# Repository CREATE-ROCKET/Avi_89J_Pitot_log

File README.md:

# 89Jのピトー管基板用です

## 現在の予定
基本的にFree RTOSでのタスク機能を利用して
 - ピトー管からデーターを得るタスク
 - それを他に送るタスク(CAN、 SPIFlash、 パリティ)
 - CANを送信するタスク
 - SPIFlashに書き込むタスク
 - MicroSDに書き込むタスク

の4つをタスクとして動作させたい。
MicroSDにログを書き込むようのタスクも作るか考え中

```mermaid
flowchart TB
  node_1("getPitotData")
  node_2("sendDataToEveryIC")
  node_3("writeDataToFlash")
  node_4("sendDataByCan")
  node_6("writeDataToSD")
  node_2 --> node_4
  node_2 --> node_3
  node_1 --> node_2
  node_2 --> node_6
```

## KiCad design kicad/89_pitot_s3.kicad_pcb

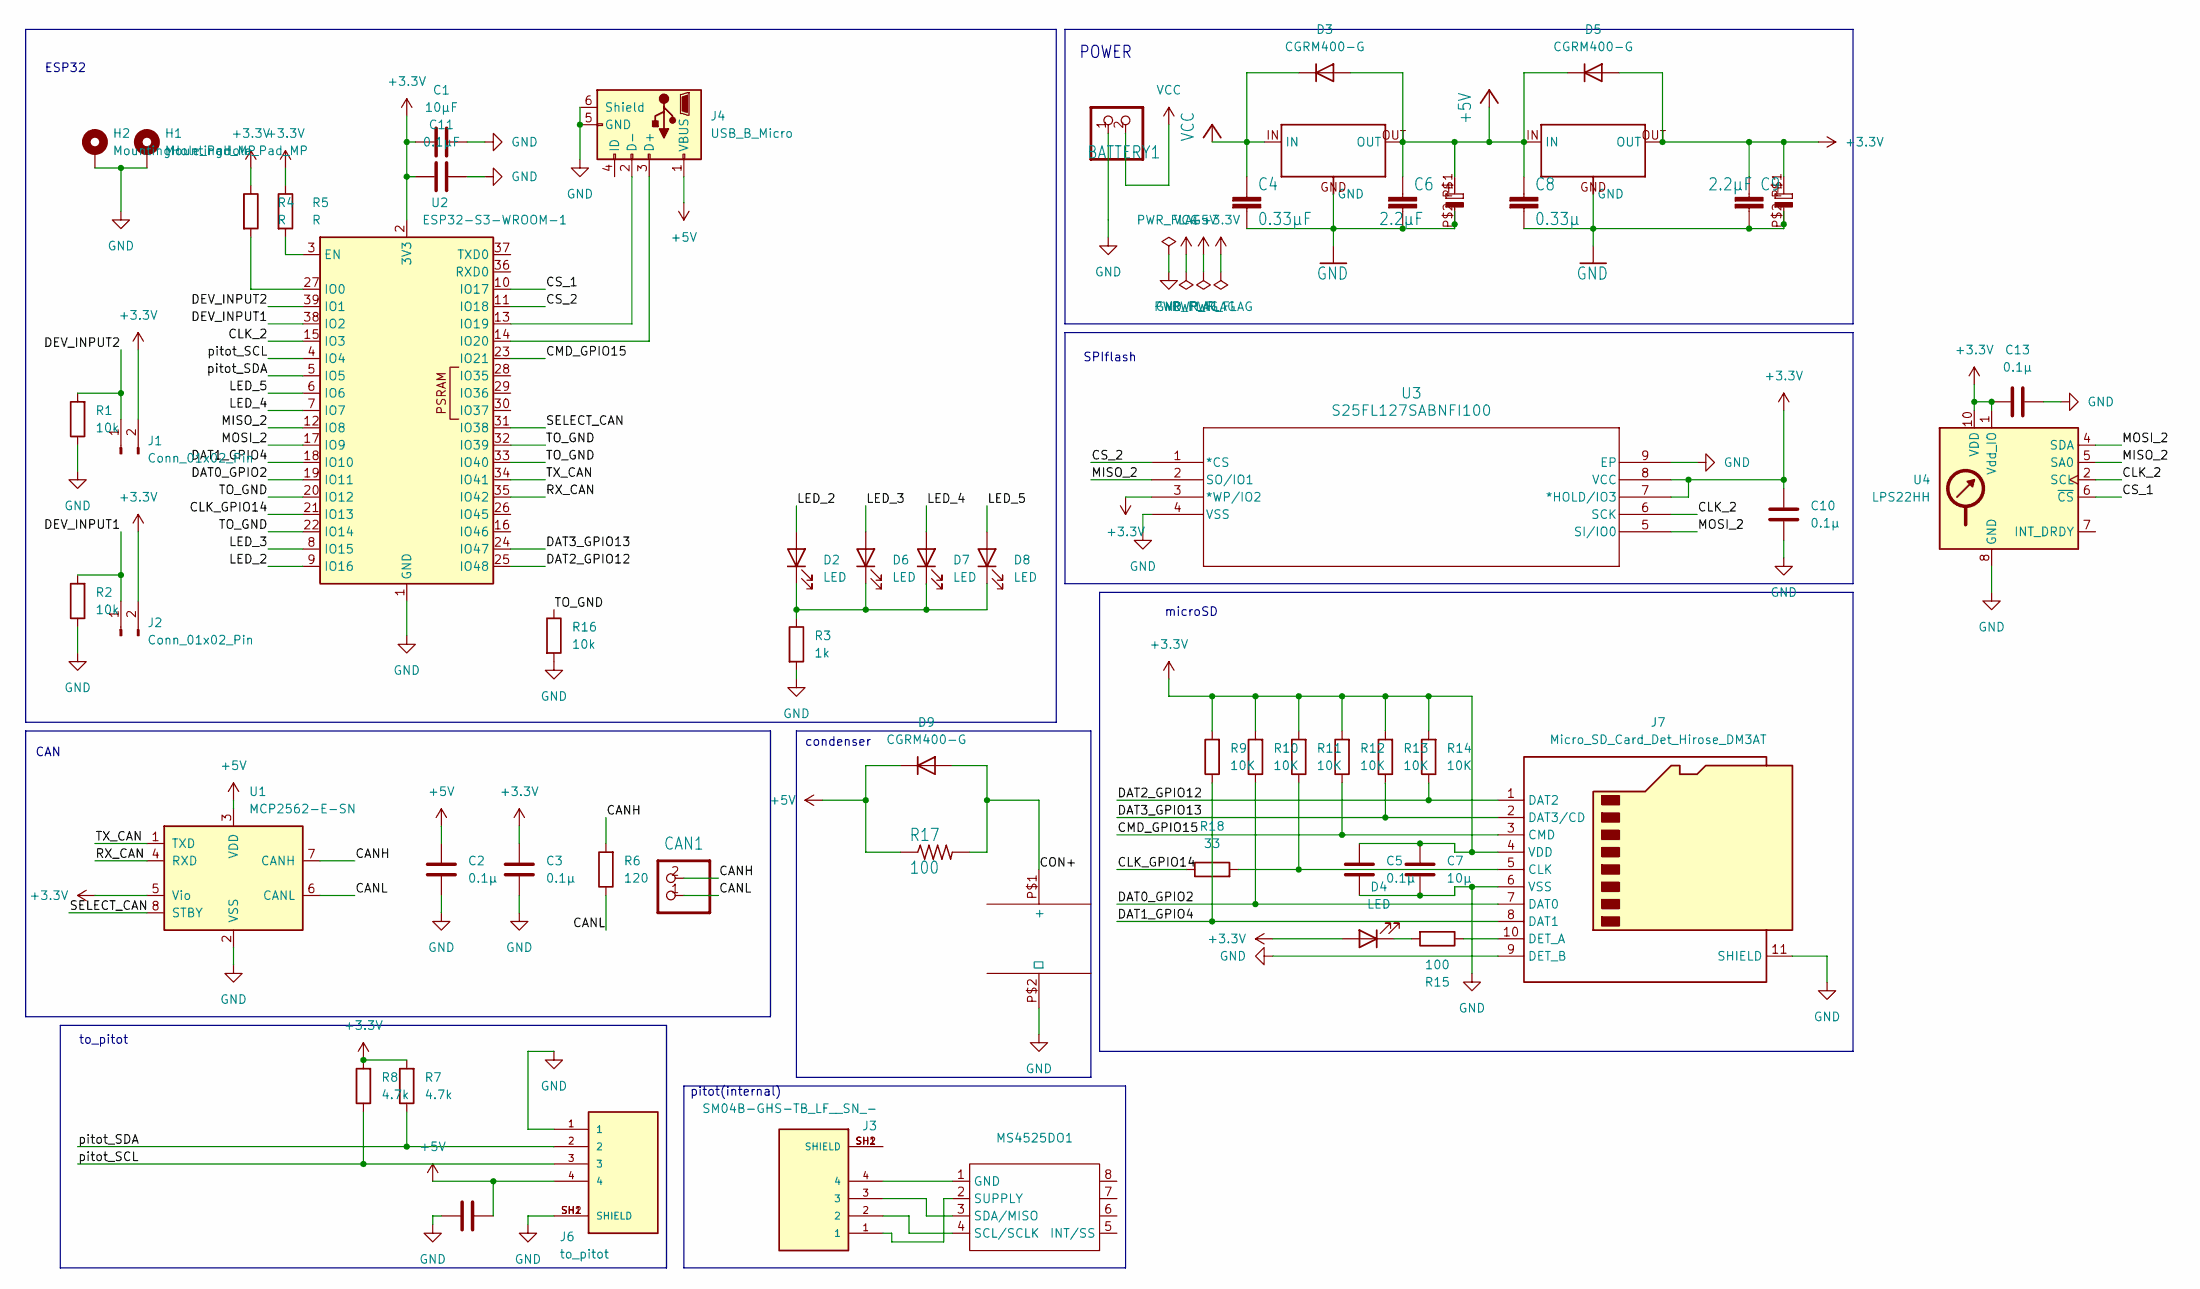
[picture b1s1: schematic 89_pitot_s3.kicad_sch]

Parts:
BATTERY1: L2; ILG2pin
C1: 10μF; C_0603_1608Metric
C2, C3, C5, C10, C12, C13: 0.1μ; C_0603_1608Metric
C4: 0.33μF; R_0603_1608Metric
C6, C9: 2.2μF; R_0603_1608Metric
C7: 10μ; D_0603_1608Metric
C8: 0.33μ; R_0603_1608Metric
C11: 0.1μF; C_0603_1608Metric
CAN1: ILG2pin
D2, D4, D6, D7, D8: LED; LED_0603_1608Metric
D3, D5, D9: CGRM400-G; D_0603_1608Metric_Pad1.05x0.95mm_HandSolder
H1, H2: MountingHole_Pad_MP; SolderWirePad_1x01_SMD_1x2mm
J1, J2: Conn_01x02_Pin; PinHeader_1x02_P2.54mm_Vertical
J3: SM04B-GHS-TB_LF__SN_-; JST_SM04B-GHS-TB_LF__SN_-; PARTREV NA
J4: USB_B_Micro; USB_Micro-B_Molex_47346-0001
J6: to_pitot; JST_GH_SM04B-GHS-TB_1x04-1MP_P1.25mm_Horizontal; PARTREV NA
J7: Micro_SD_Card_Det_Hirose_DM3AT; microSD_HC_Hirose_DM3AT-SF-PEJM5
MS4525DO1: (no value)
R1, R2: 10k; R_0603_1608Metric
R3: 1k; R_0603_1608Metric
R4, R5: R; C_0603_1608Metric
R6: 120; R_0603_1608Metric
R7, R8: 4.7k; R_0603_1608Metric
R9, R10, R11, R12, R13, R14: 10K; R_0603_1608Metric
R15: 100; R_0603_1608Metric
R16: 10k; C_0603_1608Metric
R17: 100; C_0603_1608Metric
R18: 33; C_0603_1608Metric
U1: MCP2562-E-SN; SOIC-8_3.9x4.9mm_P1.27mm
U2: ESP32-S3-WROOM-1
U3: S25FL127SABNFI100; SOC008_SPA
U4: LPS22HH; ST_HLGA-10_2x2mm_P0.5mm_LayoutBorder3x2y
U$1, U$3: NJM2391DL1-33; DPAK229P990X238-4N
U$2, U$4: UCD0J470MCL1GS; PCAP_5x5.8-ELECT_NCA
U$5: VEC5R4355QG-I; C_Disc_D8.0mm_W5.0mm_P5.00mm

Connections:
+3.3V: C1.1, C3.1, C5.1, C7.1, C9.1, C10.1, C11.1, C13.1, D4.2 (A), D5.2 (A), J1.2, J2.2, J7.4 (VDD), R4.1, R5.1, R7.2, R8.2, R9.2, R10.2, R11.2, R12.2, R13.2, R14.2, U1.5 (Vio), U2.2 (3V3), U3.3 (*WP/IO2), U3.7 (*HOLD/IO3), U3.8 (VCC), U4.1 (Vdd_IO), U4.10 (VDD), U$3.OUT, U$4.P$1 (+)
+5V: C2.1, C6.1, C8.1, C12.2, D3.2 (A), D5.1 (K), D9.1 (K), J4.1 (VBUS), J6.4, R17.1, U1.3 (VDD), U$1.OUT, U$2.P$1 (+), U$3.IN
/CANH: CAN1.2, R6.2, U1.7 (CANH); also elsewhere on the board
/CANL: CAN1.1, R6.1, U1.6 (CANL); also elsewhere on the board
/CLK_2: U2.15 (IO3), U3.6 (SCK), U4.2 (SCL)
/CLK_GPIO14: R18.1, U2.21 (IO13)
/CMD_GPIO15: J7.3 (CMD), R12.1, U2.23 (IO21)
/CON+: D9.2 (A), R17.2, U$5.P$1 (+)
/CS_1: U2.10 (IO17), U4.6 (~CS)
/CS_2: U2.11 (IO18), U3.1 (*CS)
/DAT0_GPIO2: J7.7 (DAT0), R10.1, U2.19 (IO11)
/DAT1_GPIO4: J7.8 (DAT1), R9.1, U2.18 (IO10)
/DAT2_GPIO12: J7.1 (DAT2), R14.1, U2.25 (IO48)
/DAT3_GPIO13: J7.2 (DAT3/CD), R13.1, U2.24 (IO47)
/DEV_INPUT1: J2.1, R2.2, U2.38 (IO2)
/DEV_INPUT2: J1.1, R1.2, U2.39 (IO1)
/LED_2: D2.2 (A), U2.9 (IO16)
/LED_3: D6.2 (A), U2.8 (IO15)
/LED_4: D7.2 (A), U2.7 (IO7)
/LED_5: D8.2 (A), U2.6 (IO6)
/MISO_2: U2.12 (IO8), U3.2 (SO/IO1), U4.5 (SA0)
/MOSI_2: U2.17 (IO9), U3.5 (SI/IO0), U4.4 (SDA)
/RX_CAN: U1.4 (RXD), U2.35 (IO42)
/SELECT_CAN: U1.8 (STBY), U2.31 (IO38)
/TO_GND: R16.1, U2.20 (IO12), U2.22 (IO14), U2.32 (IO39), U2.33 (IO40)
/TX_CAN: U1.1 (TXD), U2.34 (IO41)
/pitot_SCL: J6.3, R8.1, U2.4 (IO4)
/pitot_SDA: J6.2, R7.1, U2.5 (IO5)
GND: BATTERY1.1, C1.2, C2.2, C3.2, C4.2, C5.2, C6.2, C7.2, C8.2, C9.2, C10.2, C11.2, C12.1, C13.2, H1.MP, H2.MP, J4.5 (GND), J4.6 (Shield), J6.1, J6.SH1 (SHIELD), J6.SH2 (SHIELD), J7.6 (VSS), J7.9 (DET_B), J7.11 (SHIELD), R1.1, R2.1, R3.2, R16.2, U1.2 (VSS), U2.1 (GND), U2.40 (GND), U2.41 (GND), U3.4 (VSS), U3.9 (EP), U4.3 (GND), U4.8 (GND), U4.9 (GND), U$1.GND, U$2.P$2 (ー), U$3.GND, U$4.P$2 (ー), U$5.P$2 (ー); also elsewhere on the board
unnamed: D2.1 (K), D6.1 (K), D7.1 (K), D8.1 (K), R3.1
unnamed: D4.1 (K), R15.2
unnamed: J3.1, MS4525DO1.2 (SUPPLY)
unnamed: J3.2, MS4525DO1.4 (SCL/SCLK)
unnamed: J3.3, MS4525DO1.3 (SDA/MISO)
unnamed: J3.4, MS4525DO1.1 (GND)
unnamed: J3.SH1 (SHIELD), J3.SH2 (SHIELD)
unnamed: J4.3 (D+), U2.14 (IO20)
unnamed: J4.2 (D-), U2.13 (IO19)
unnamed: J7.5 (CLK), R11.1, R18.2
unnamed: J7.10 (DET_A), R15.1
unnamed: R5.2, U2.3 (EN)
unnamed: R4.2, U2.27 (IO0)
VCC: BATTERY1.2, C4.1, D3.1 (K), U$1.IN; also elsewhere on the board

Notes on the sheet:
POWER
pitot(internal)
condenser
microSD
ESP32
to_pitot
SPIflash
CAN

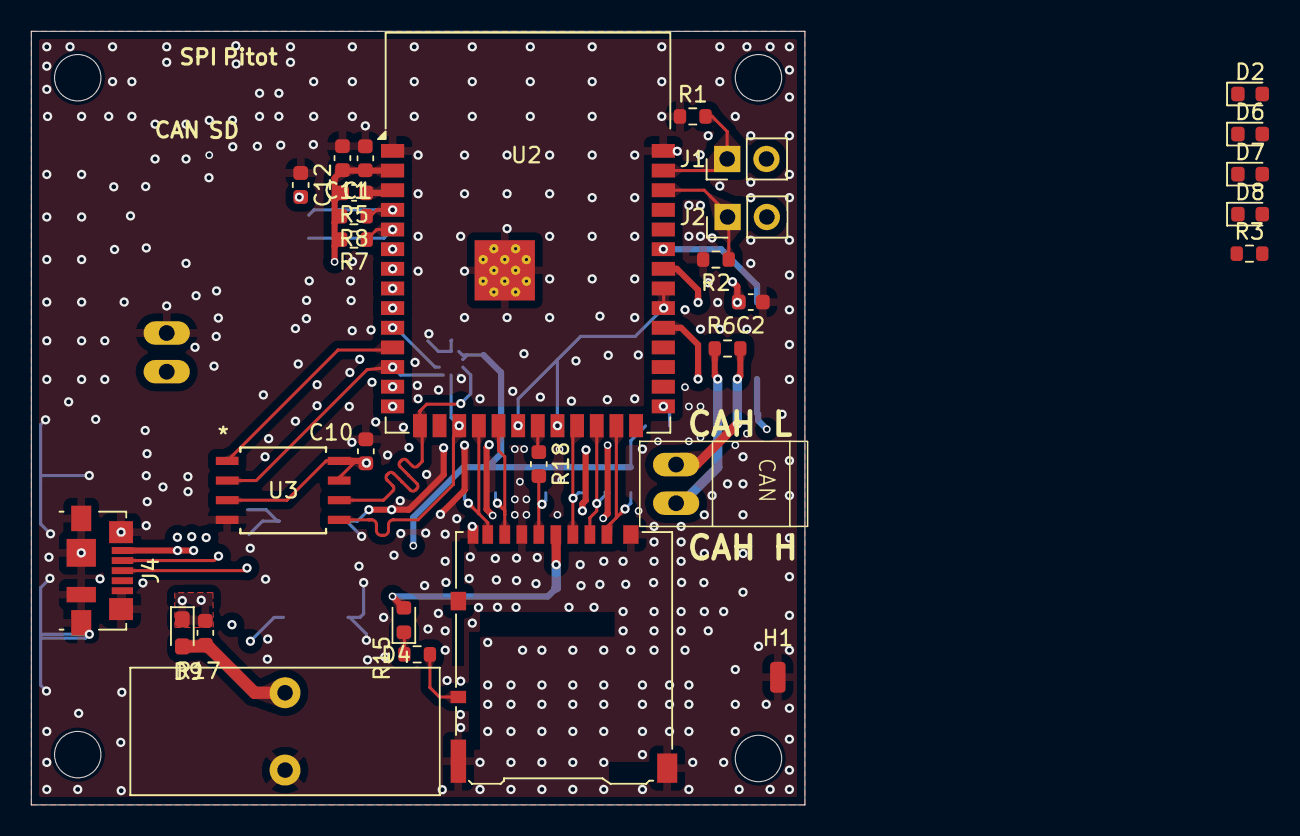
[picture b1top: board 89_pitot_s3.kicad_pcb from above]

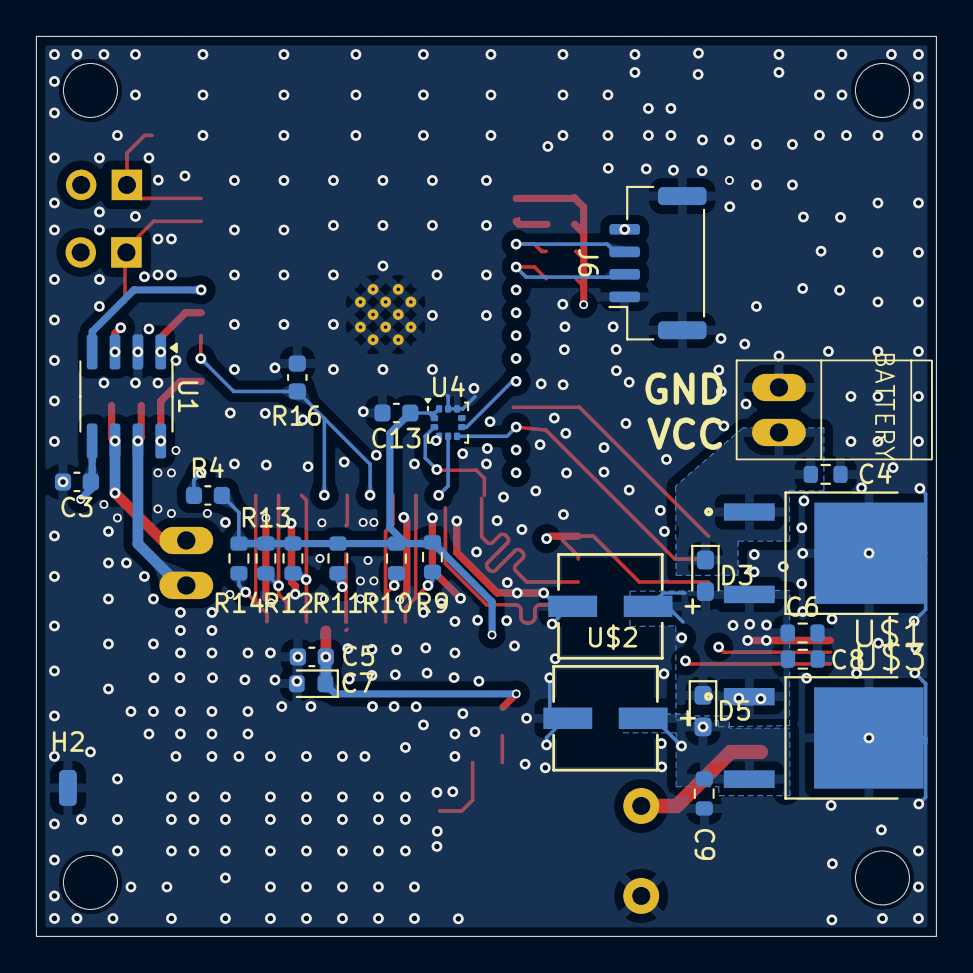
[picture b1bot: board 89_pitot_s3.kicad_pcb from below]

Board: 8 copper layers, 50.0 x 50.0 mm, 57 parts (27 on the bottom side), 38 nets.

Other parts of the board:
BATTERY: L2; ILG2pin
CAN: ILG2pin

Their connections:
/CANH: CAN.2; also elsewhere on the board
/CANL: CAN.1; also elsewhere on the board
GND: BATTERY.1; also elsewhere on the board
VCC: BATTERY.2; also elsewhere on the board

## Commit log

2024-10-04 initial commit SD SPI flash test
2024-10-04 [refactor]change submodules
2024-11-30 実機で動作用コードを書き始めた。現在、initはすべて書き終えた
2024-12-04 [add] ピトー管とFlash、SDに関しては一旦書き終わった
2024-12-10 microSDのゲートキーパータスクを作成 詳細な変更点 - Queueで渡される実体をポインタに変更 - xTaskはSuspendせずにxQueueReceiveの待ち時間を無制限とすることにする xQueueReceiveの待ち時間はvTaskDelayと同等なはず - microSDへの書き込み用のゲートキーパータスクを作成 - microSDへlogを書き込むことにした。 - erro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
2024-12-11 [fix]error_logを動作させた。 snprintfがうまく動作しないため、悩み中。
2024-12-12 [fix]distributeToEveryICTaskHandleが動作しないのを修正 Union型が悪さしてた
2024-12-14 [add] add panic BackTrace wrapper
2025-01-04 [add] print flash old data
2025-01-09 [fix] critical sectionはwatch dog timerでpanicする
2025-01-12 [add] esp32 s3 support (WIP)
2025-01-23 [delete] delete memory controller
2025-01-23 [fix] double free
2025-01-24 [fix] queue send bug
2025-01-24 [fix] esp32 panicked when SD init returned 1 or 2
2025-02-05 [add] ESP32 S3 support
2025-02-15 [add] esp32 s3 support (MicroSD)
2025-02-15 [add] CAN support
2025-03-08 [add] analyzer written in rust
2025-03-09 [fix] fix some problems
2025-03-12 [change] refactor project structure
2025-03-14 [fix] fix DataToChar
2025-03-14 [add] show speed (m/s)
2025-03-14 [fix] watch dog triggered
2025-03-15 [add] result
2025-03-15 [add] data analyzed result
2025-03-15 [fix] wrong air density at data analyzer
2025-03-16 [add] SPIFFS support
2025-03-17 [add] write data to flash
2025-03-19 [add] SPIFFS support (WIP)
2025-03-19 [add] SPIFFS by arduino library
2025-03-19 [fix] SPIFFS error (WIP)
2025-03-19 [remove] SPIFFS support
2025-03-20 [fix] flash run (WIP)
2025-03-20 [fix] flash not running
2025-03-22 [fix] flash log (Not working)
2025-09-07 [add] kicad file
